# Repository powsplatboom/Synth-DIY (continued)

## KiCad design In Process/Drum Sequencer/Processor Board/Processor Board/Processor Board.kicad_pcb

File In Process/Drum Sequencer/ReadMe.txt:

Drum sequencer for eurorack drums. Implements piezos for drum pads, multiplexed buttons and LEDs for visual information, and other UI and I/O modules.
Coding still in process, but stalled while I learn Microchip Studio.

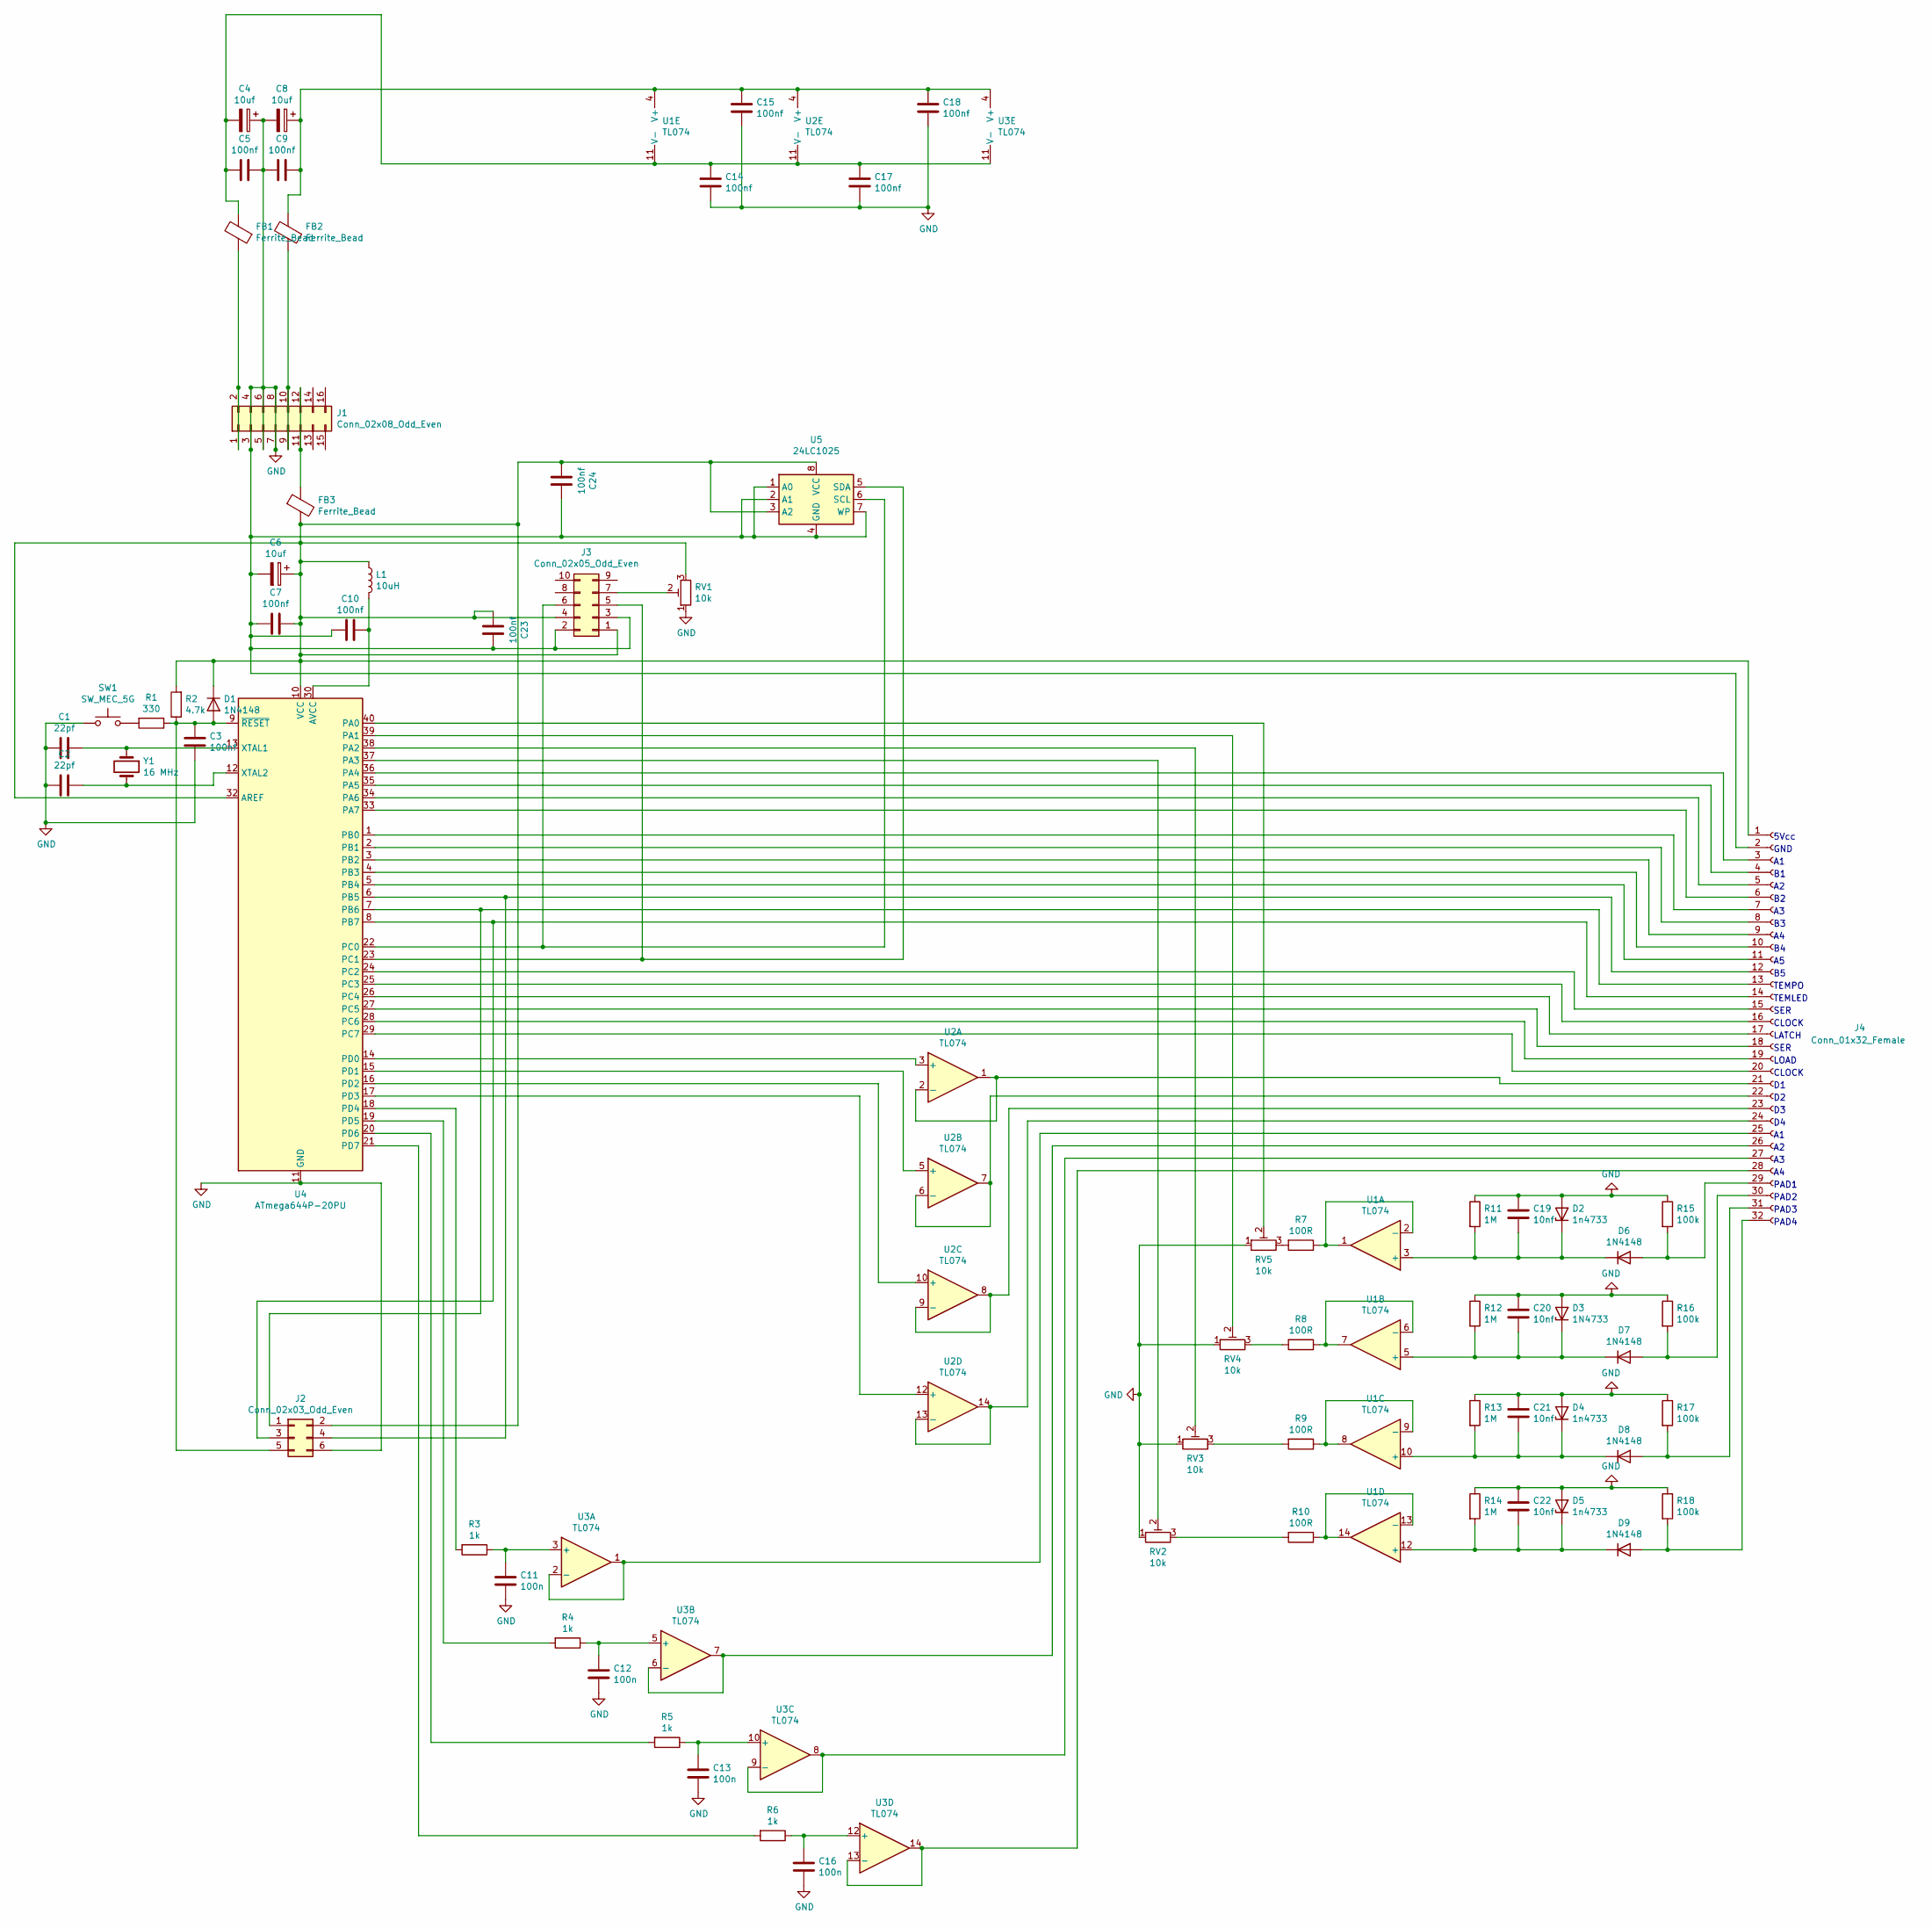
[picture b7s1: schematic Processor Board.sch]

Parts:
C1, C2: 22pf; C_0805_2012Metric_Pad1.18x1.45mm_HandSolder
C3, C5, C7, C9, C10, C14, C15, C17, C18, C23, C24: 100nf; C_0805_2012Metric_Pad1.18x1.45mm_HandSolder
C4, C6, C8: 10uf; CP_Radial_D5.0mm_P2.00mm
C11, C12, C13, C16: 100n; C_0805_2012Metric_Pad1.18x1.45mm_HandSolder
C19, C20, C21, C22: 10nf; C_0805_2012Metric_Pad1.18x1.45mm_HandSolder
D1, D6, D7, D8, D9: 1N4148; D_DO-35_SOD27_P7.62mm_Horizontal
D2, D4, D5: 1n4733; D_DO-41_SOD81_P7.62mm_Horizontal
D3: 1N4733; D_DO-41_SOD81_P7.62mm_Horizontal
FB1, FB2, FB3: Ferrite_Bead; L_Axial_L9.5mm_D4.0mm_P5.08mm_Vertical_Fastron_SMCC
J1: Conn_02x08_Odd_Even; IDC-Header_2x08_P2.54mm_Vertical
J2: Conn_02x03_Odd_Even; IDC-Header_2x03_P2.54mm_Vertical
J3: Conn_02x05_Odd_Even; PinSocket_2x05_P2.54mm_Vertical
J4: Conn_01x32_Female; PinSocket_1x32_P2.54mm_Vertical
L1: 10uH; L_Axial_L5.0mm_D3.6mm_P10.00mm_Horizontal_Murata_BL01RN1A2A2
R1: 330; R_0805_2012Metric_Pad1.20x1.40mm_HandSolder
R2: 4.7k; R_1210_3225Metric_Pad1.30x2.65mm_HandSolder
R3, R4, R5, R6: 1k; R_1206_3216Metric_Pad1.30x1.75mm_HandSolder
R7, R8, R9, R10: 100R; R_1206_3216Metric_Pad1.30x1.75mm_HandSolder
R11, R12, R13, R14: 1M; R_1206_3216Metric_Pad1.30x1.75mm_HandSolder
R15, R16, R17, R18: 100k; R_1206_3216Metric_Pad1.30x1.75mm_HandSolder
RV1, RV2, RV3, RV4, RV5: 10k; Potentiometer_Bourns_3296W_Vertical
SW1: SW_MEC_5G; SW_DIP_SPSTx01_Slide_6.7x4.1mm_W6.73mm_P2.54mm_LowProfile_J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
U1, U2, U3: TL074; SO-14_3.9x8.65mm_P1.27mm
U4: ATmega644P-20PU; DIP-40_W15.24mm
U5: 24LC1025; SOIC-8-1EP_3.9x4.9mm_P1.27mm_EP2.29x3mm
Y1: 16 MHz; Crystal_HC49-4H_Vertical

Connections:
GND: C1.2, C2.2, C3.2, C4.1, C5.2, C6.2, C7.1, C8.2, C9.1, C10.1, C11.2, C12.2, C13.2, C14.2, C15.2, C16.2, C17.2, C18.2, C19.1, C20.1, C21.1, C22.1, C23.2, C24.2, D2.2 (A), D3.2 (A), D4.2 (A), D5.2 (A), J1.3, J1.4, J1.5, J1.6, J1.7, J1.8, J2.6, J3.2, J3.3, J4.2, R11.1, R12.1, R13.1, R14.1, R15.1, R16.1, R17.1, R18.1, RV1.1, RV2.1, RV3.1, RV4.1, RV5.1, SW1.1 (A), U4.11 (GND), U4.31 (GND), U5.1 (A0), U5.2 (A1), U5.4 (GND), U5.7 (WP)
unnamed: C1.1, U4.13 (XTAL1), Y1.1
unnamed: C2.1, U4.12 (XTAL2), Y1.2
unnamed: C3.1, D1.2 (A), J2.5, R1.1, R2.1, U4.9 (~RESET)
unnamed: C10.2, L1.2, U4.30 (AVCC)
unnamed: C11.1, R3.1, U3.3 (+)
unnamed: C12.1, R4.1, U3.5 (+)
unnamed: C13.1, R5.1, U3.10 (+)
unnamed: C4.2, C5.1, C14.1, C17.1, FB1.2, U1.11 (V-), U2.11 (V-), U3.11 (V-)
unnamed: C8.1, C9.2, C15.1, C18.1, FB2.2, U1.4 (V+), U2.4 (V+), U3.4 (V+)
unnamed: C16.1, R6.1, U3.12 (+)
unnamed: C19.2, D2.1 (K), D6.1 (K), R11.2, U1.3 (+)
unnamed: C20.2, D3.1 (K), D7.1 (K), R12.2, U1.5 (+)
unnamed: C21.2, D4.1 (K), D8.1 (K), R13.2, U1.10 (+)
unnamed: C22.2, D5.1 (K), D9.1 (K), R14.2, U1.12 (+)
unnamed: C6.1, C7.2, C23.1, C24.1, D1.1 (K), FB3.2, J2.2, J3.1, J3.4, J4.1, L1.1, R2.2, RV1.3, U4.10 (VCC), U4.32 (AREF), U5.3 (A2), U5.8 (VCC)
unnamed: D6.2 (A), J4.29, R15.2
unnamed: D7.2 (A), J4.30, R16.2
unnamed: D8.2 (A), J4.31, R17.2
unnamed: D9.2 (A), J4.32, R18.2
unnamed: FB1.1, J1.1, J1.2
unnamed: FB2.1, J1.9, J1.10
unnamed: FB3.1, J1.11, J1.12
unnamed: J2.1, J4.13, U4.7 (PB6)
unnamed: J2.3, J4.14, U4.8 (PB7)
unnamed: J2.4, J4.12, U4.6 (PB5)
unnamed: J3.5, U4.23 (PC1), U5.5 (SDA)
unnamed: J3.6, U4.22 (PC0), U5.6 (SCL)
unnamed: J3.7, RV1.2
unnamed: J4.3, U4.36 (PA4)
unnamed: J4.4, U4.35 (PA5)
unnamed: J4.5, U4.34 (PA6)
unnamed: J4.6, U4.33 (PA7)
unnamed: J4.7, U4.1 (PB0)
unnamed: J4.8, U4.2 (PB1)
unnamed: J4.9, U4.3 (PB2)
unnamed: J4.10, U4.4 (PB3)
unnamed: J4.11, U4.5 (PB4)
unnamed: J4.15, U4.24 (PC2)
unnamed: J4.16, U4.25 (PC3)
unnamed: J4.17, U4.26 (PC4)
unnamed: J4.18, U4.27 (PC5)
unnamed: J4.19, U4.28 (PC6)
unnamed: J4.20, U4.29 (PC7)
unnamed: J4.21, U2.1, U2.2 (-)
unnamed: J4.22, U2.6 (-), U2.7
unnamed: J4.23, U2.8, U2.9 (-)
unnamed: J4.24, U2.13 (-), U2.14
unnamed: J4.25, U3.1, U3.2 (-)
unnamed: J4.26, U3.6 (-), U3.7
unnamed: J4.27, U3.8, U3.9 (-)
unnamed: J4.28, U3.13 (-), U3.14
unnamed: R1.2, SW1.2 (B)
unnamed: R3.2, U4.18 (PD4)
unnamed: R4.2, U4.19 (PD5)
unnamed: R5.2, U4.20 (PD6)
unnamed: R6.2, U4.21 (PD7)
unnamed: R7.1, U1.1, U1.2 (-)
unnamed: R7.2, RV5.3
unnamed: R8.1, U1.6 (-), U1.7
unnamed: R8.2, RV4.3
unnamed: R9.1, U1.8, U1.9 (-)
unnamed: R9.2, RV3.3
unnamed: R10.1, U1.13 (-), U1.14
unnamed: R10.2, RV2.3
unnamed: RV2.2, U4.37 (PA3)
unnamed: RV3.2, U4.38 (PA2)
unnamed: RV4.2, U4.39 (PA1)
unnamed: RV5.2, U4.40 (PA0)
unnamed: U2.3 (+), U4.14 (PD0)
unnamed: U2.5 (+), U4.15 (PD1)
unnamed: U2.10 (+), U4.16 (PD2)
unnamed: U2.12 (+), U4.17 (PD3)

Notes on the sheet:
5Vcc
GND
TEMPO
TEMLED
LATCH
CLOCK
SER
LOAD
PAD1
PAD2
PAD3
PAD4

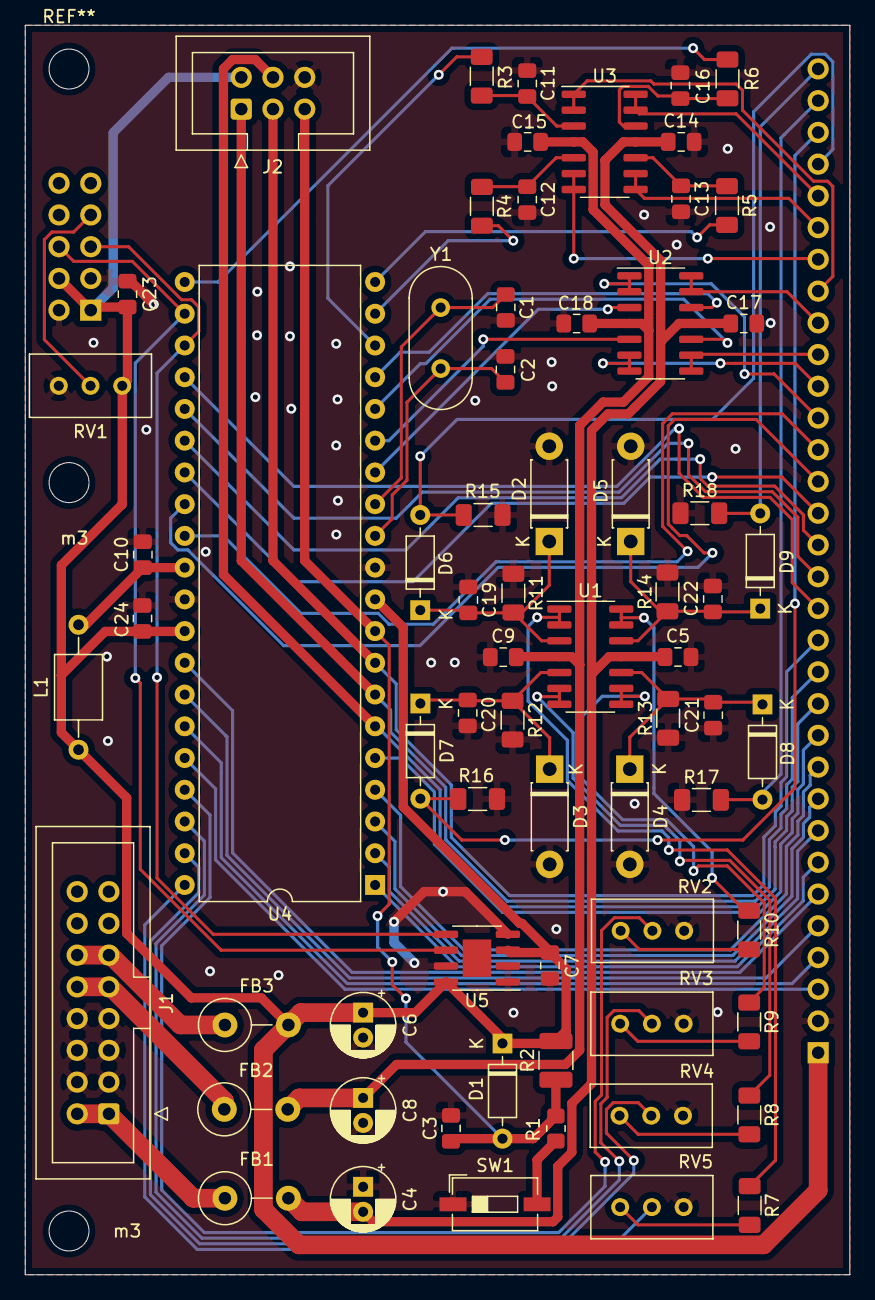
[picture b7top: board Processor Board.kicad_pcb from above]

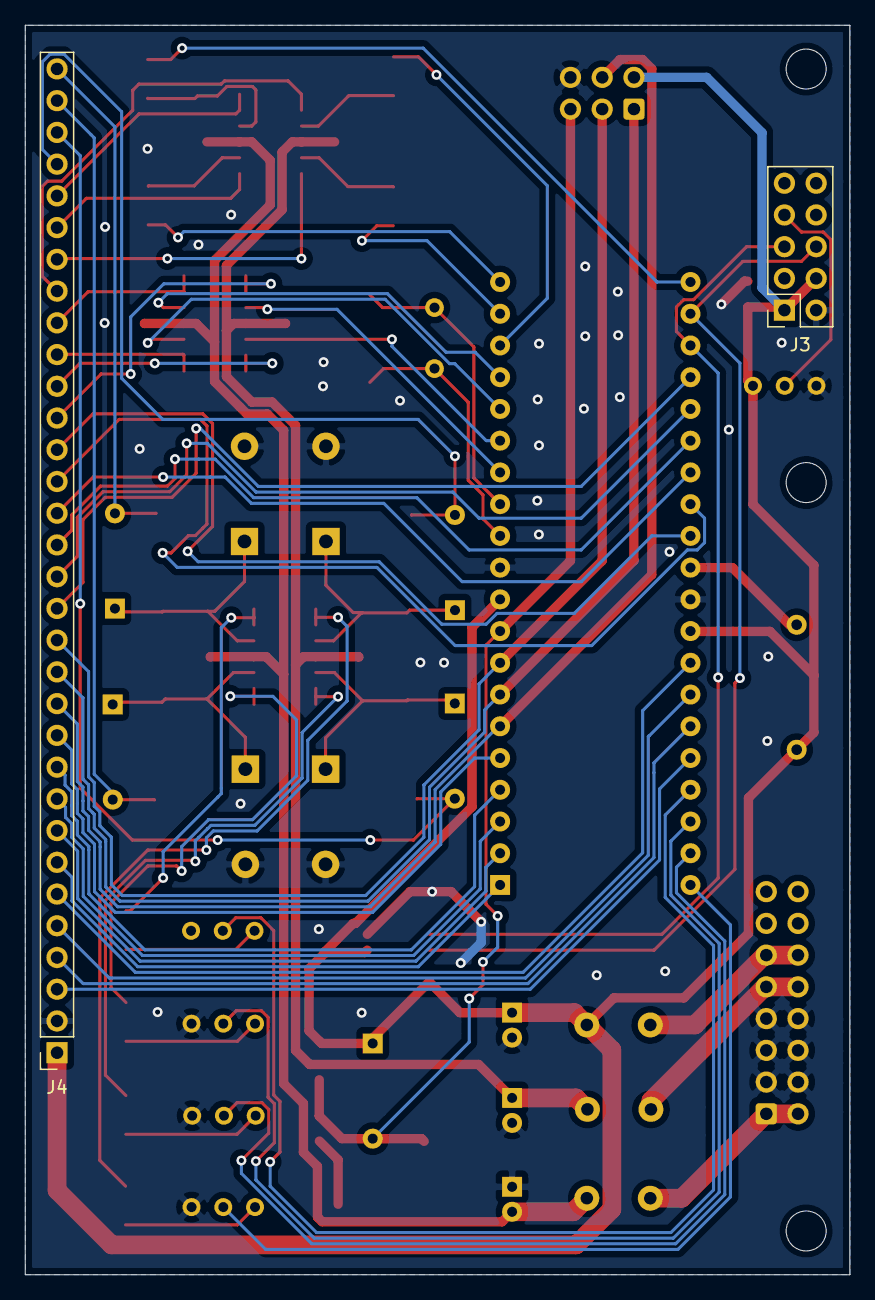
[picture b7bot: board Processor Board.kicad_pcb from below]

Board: 2 copper layers, 66.0 x 100.0 mm, 73 parts (2 on the bottom side), 73 nets.

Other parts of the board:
m3, m3#2: MountingHole_3.2mm_M3

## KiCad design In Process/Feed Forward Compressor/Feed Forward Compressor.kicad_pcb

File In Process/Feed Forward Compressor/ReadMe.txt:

Needs some corrections to the board. Missed a ground on the analog engine, and need to rework LED Driver to behave more predictably to display compression.

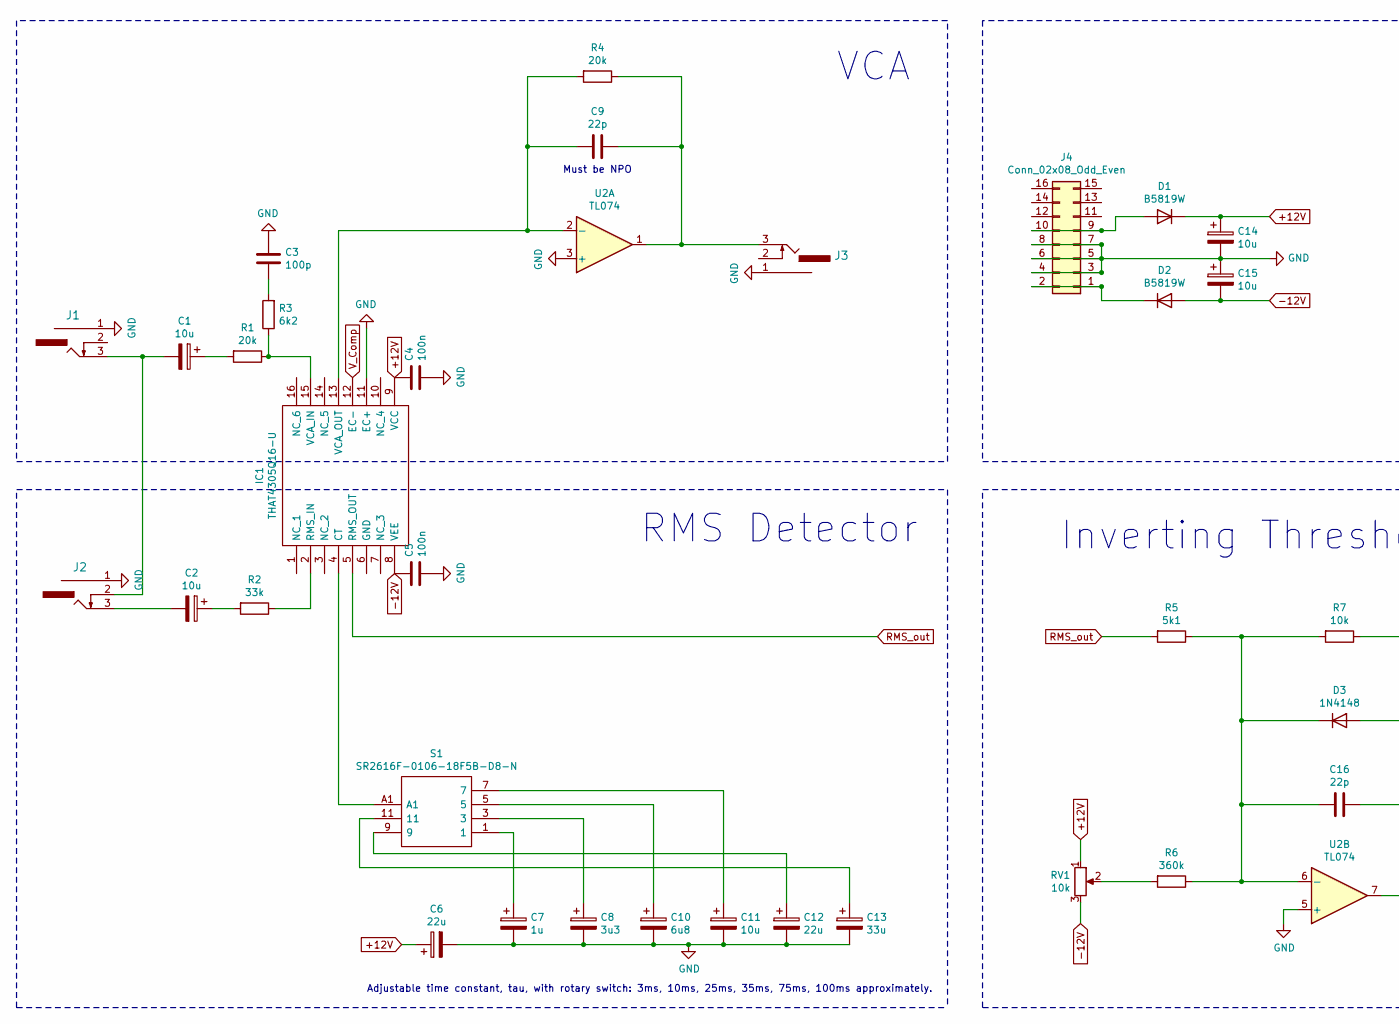
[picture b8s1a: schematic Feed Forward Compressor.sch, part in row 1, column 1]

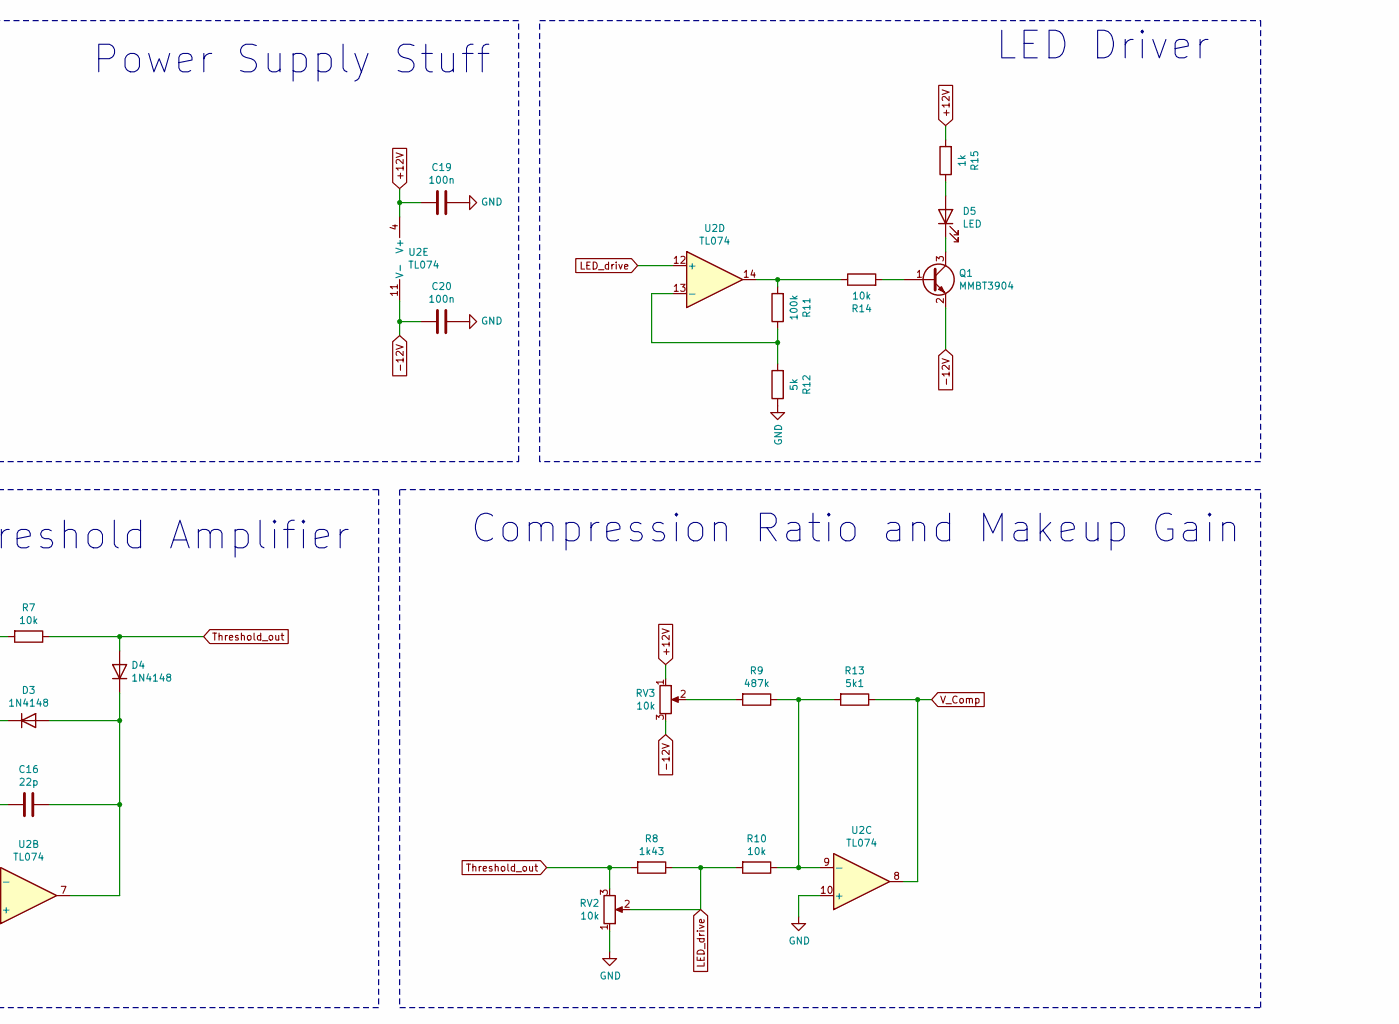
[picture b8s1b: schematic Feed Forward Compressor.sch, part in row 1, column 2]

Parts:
C1, C2, C11, C14, C15: 10u; CP_Elec_4x5.3
C3: 100p; C_0603_1608Metric
C4, C5, C19, C20: 100n; C_0603_1608Metric
C6, C12: 22u; CP_Elec_4x5.3
C7: 1u; CP_Elec_4x5.3
C8: 3u3; CP_Elec_4x5.3
C9, C16: 22p; C_0603_1608Metric
C10: 6u8; CP_Elec_4x5.4
C13: 33u; CP_Elec_5x5.3
D1, D2: B5819W; D_SOD-123
D3, D4: 1N4148; D_SOD-123
D5: LED; LED_1206_3216Metric
IC1: THAT4305Q16-U; SSOP-16_3.9x4.9mm_P0.635mm; Manufacturer_Part_Number THAT4305Q16-U
J1, J2, J3: PJ301_THONKICONN; PJ-3001_Mono_Phone
J4: Conn_02x08_Odd_Even; IDC-Header_2x08_P2.54mm_Vertical
Q1: MMBT3904; SOT-23
R1, R4: 20k; R_0603_1608Metric
R2: 33k; R_0603_1608Metric
R3: 6k2; R_0603_1608Metric
R5, R13: 5k1; R_0603_1608Metric
R6: 360k; R_0603_1608Metric
R7, R10, R14: 10k; R_0603_1608Metric
R8: 1k43; R_0603_1608Metric
R9: 487k; R_0603_1608Metric
R11: 100k; R_0603_1608Metric
R12: 5k; R_0603_1608Metric
R15: 1k; R_0603_1608Metric
RV1, RV2, RV3: 10k; Potentiometer_Alpha_RD901F-40-00D_Single_Vertical
S1: SR2616F-0106-18F5B-D8-N; SR2616F-0106; Manufacturer_Part_Number SR2616F-0106-18F5B-D8-N; Mouser Part Number 105-SR2616F-16-18FN
U2: TL074; SOIC-14_3.9x8.7mm_P1.27mm

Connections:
+12V: C4.1, C6.1, C14.1, C19.2, D1.1 (K), IC1.9 (VCC), R15.2, RV1.1, RV3.1, U2.4 (V+)
-12V: C5.1, C15.2, C20.2, D2.2 (A), IC1.8 (VEE), Q1.2 (E), RV1.3, RV3.3, U2.11 (V-)
GND: C3.1, C4.2, C5.2, C6.2, C7.2, C8.2, C10.2, C11.2, C12.2, C13.2, C14.2, C15.1, C19.1, C20.1, IC1.11 (EC+), J1.1, J2.1, J3.1, J4.3, J4.4, J4.5, J4.6, J4.7, J4.8, R12.1, RV2.1, U2.3 (+), U2.5 (+), U2.10 (+)
LED_drive: R8.1, R10.2, RV2.2, U2.12 (+)
unnamed: C1.1, R1.2
unnamed: C1.2, J1.3, J2.2
unnamed: C2.1, R2.2
unnamed: C2.2, J2.3
unnamed: C3.2, R3.2
unnamed: C7.1, S1.1
unnamed: C8.1, S1.3
unnamed: C9.1, IC1.13 (VCA_OUT), R4.2, U2.2 (-)
unnamed: C9.2, J3.3, R4.1, U2.1
unnamed: C10.1, S1.5
unnamed: C11.1, S1.7
unnamed: C12.1, S1.9
unnamed: C13.1, S1.11
unnamed: C16.1, D3.1 (K), R5.1, R6.1, R7.2, U2.6 (-)
unnamed: C16.2, D3.2 (A), D4.1 (K), U2.7
unnamed: D1.2 (A), J4.9, J4.10
unnamed: D2.1 (K), J4.1, J4.2
unnamed: D5.1 (K), Q1.3 (C)
unnamed: D5.2 (A), R15.1
unnamed: IC1.2 (RMS_IN), R2.1
unnamed: IC1.4 (CT), S1.A1
unnamed: IC1.15 (VCA_IN), R1.1, R3.1
unnamed: Q1.1 (B), R14.2
unnamed: R6.2, RV1.2
unnamed: R9.2, RV3.2
unnamed: R9.1, R10.1, R13.2, U2.9 (-)
unnamed: R11.1, R12.2, U2.13 (-)
unnamed: R11.2, R14.1, U2.14
RMS_out: IC1.5 (RMS_OUT), R5.2
Threshold_out: D4.2 (A), R7.1, R8.2, RV2.3
V_Comp: IC1.12 (EC-), R13.1, U2.8

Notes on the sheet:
VCA
RMS Detector
Adjustable time constant, tau, with rotary switch: 3ms, 10ms, 25ms, 35ms, 75ms, 100ms approximately.
Must be NPO
Inverting Threshold Amplifier
Compression Ratio and Makeup Gain
Power Supply Stuff
LED Driver

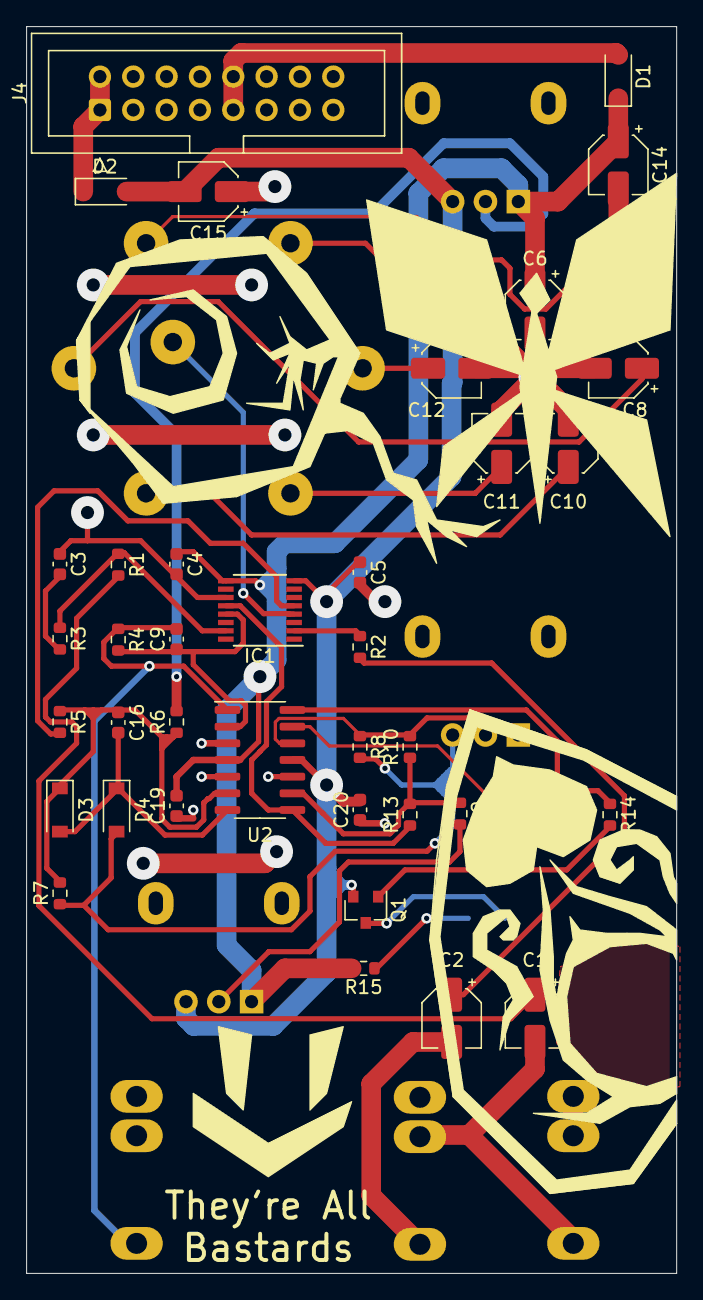
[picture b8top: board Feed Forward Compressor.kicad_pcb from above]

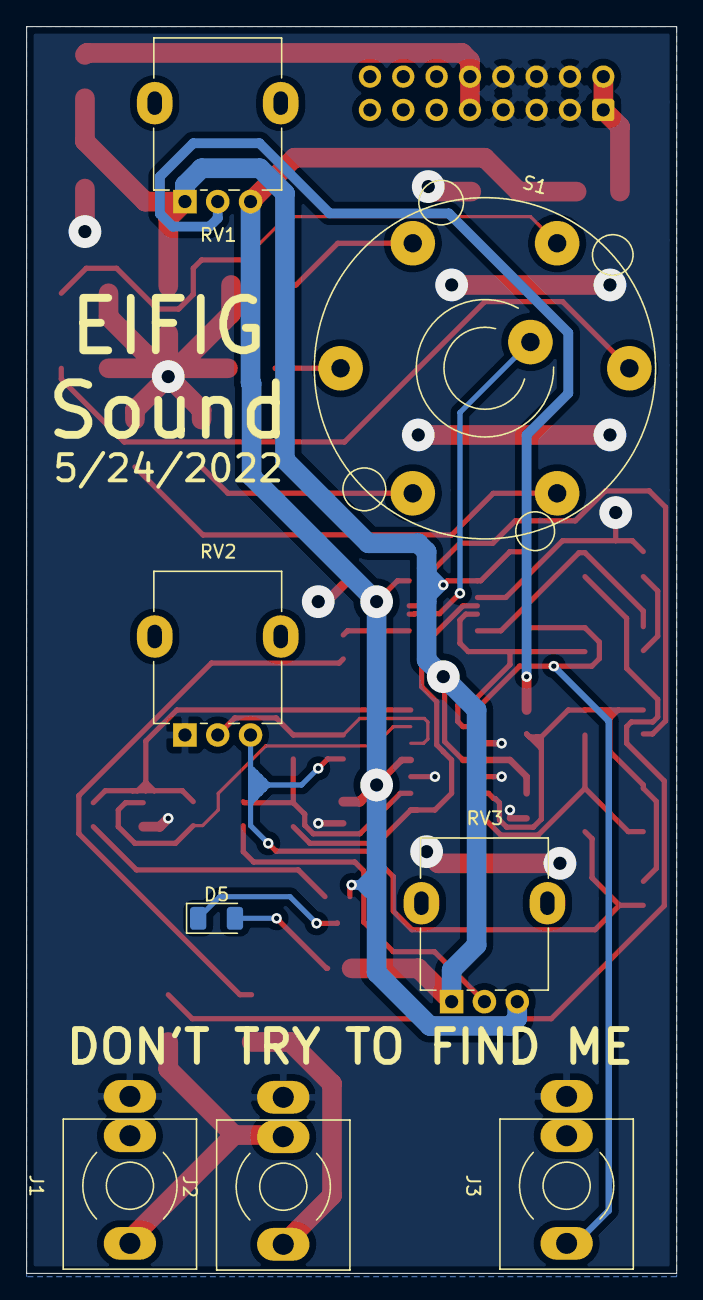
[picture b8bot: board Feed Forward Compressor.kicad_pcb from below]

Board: 2 copper layers, 49.5 x 95.0 mm, 49 parts (8 on the bottom side), 35 nets.

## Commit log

2022-12-14 Create gitkeep
